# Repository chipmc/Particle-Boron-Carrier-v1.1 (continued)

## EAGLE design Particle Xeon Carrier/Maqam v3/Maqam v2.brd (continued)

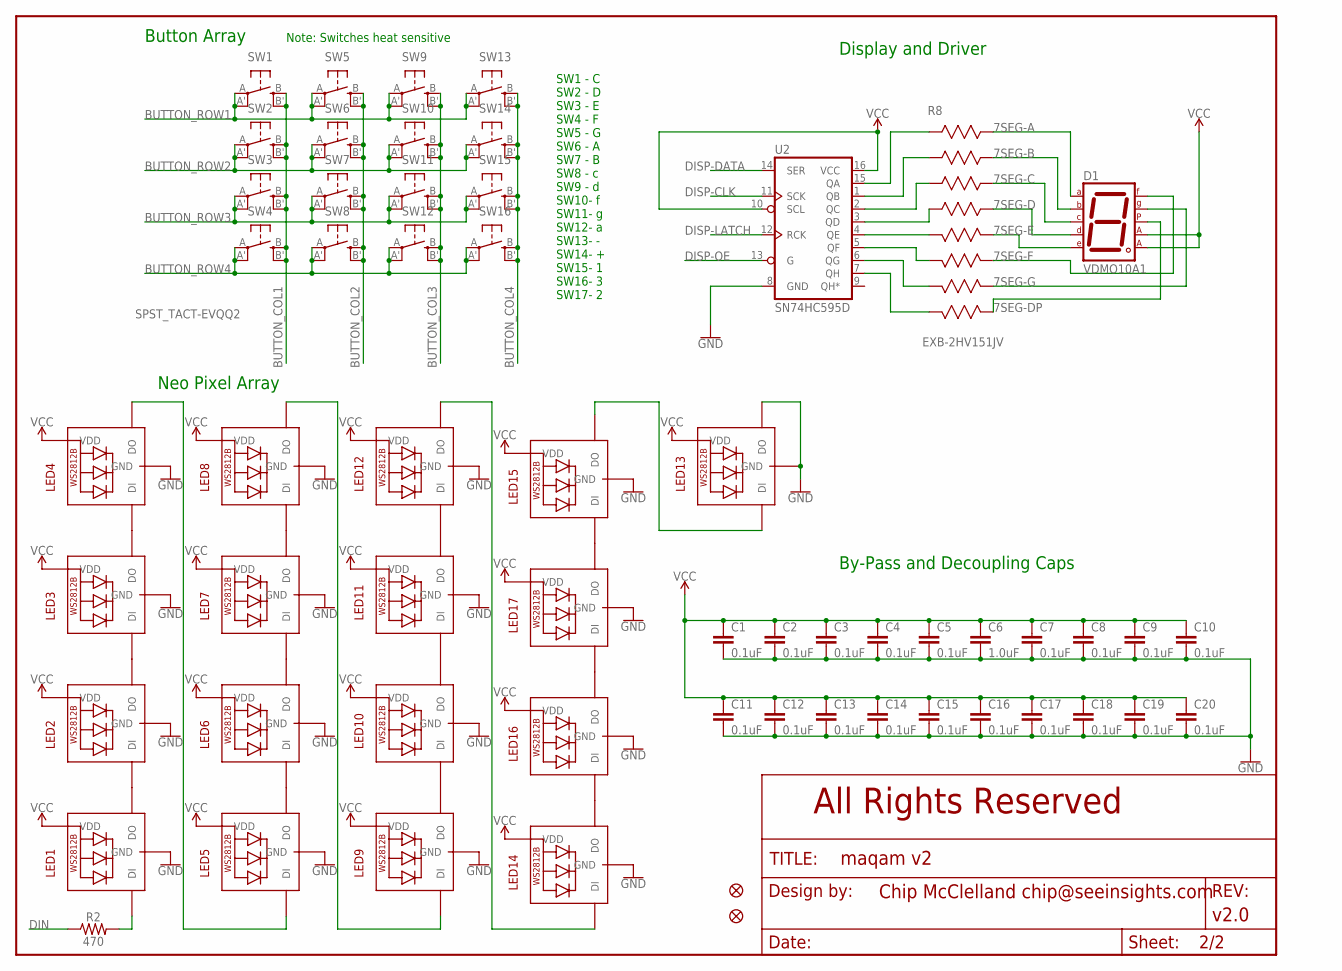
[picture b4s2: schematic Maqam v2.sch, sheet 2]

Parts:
C1, C2, C3, C4, C5, C7, C8, C9, C10, C11, C12, C13, C14, C15, C16, C17, C18, C19, C20: 0.1uF; 0805
C6: 1.0uF; 0805
D1: VDMO10A1; 7-SEG-SMD
FD1, FD2: FIDUCIALUFIDUCIAL; FIDUCIAL-MICRO
FRAME1: FRAME-LETTERNO_PACKAGE; DUMMY
LED1, LED2, LED3, LED4, LED5, LED6, LED7, LED8, LED9, LED10, LED11, LED12, LED13, LED14, LED15, LED16, LED17: WS2812B3535; LED3535
R2: 470; 0805
R8: EXB-2HV151JV; EXB2HV-L
SW1, SW2, SW3, SW4, SW5, SW6, SW7, SW8, SW9, SW10, SW11, SW12, SW13, SW14, SW15, SW16: SPST_TACT-EVQQ2; EVQ-Q2
U2: SN74HC595D; SO16

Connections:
7SEG-A: D1.7SEG7 (A), R8.16 (162)
7SEG-B: D1.7SEG6 (B), R8.15 (154)
7SEG-C: D1.7SEG4 (C), R8.14 (146)
7SEG-D: D1.7SEG2 (D), R8.13 (138)
7SEG-DP: D1.7SEG5 (DP), R8.9 (912)
7SEG-E: D1.7SEG1 (E), R8.12 (1211)
7SEG-F: D1.7SEG9 (F), R8.11 (1110)
7SEG-G: D1.7SEG10 (G), R8.10 (109)
BUTTON_COL1: SW1.B (S), SW1.B' (S1), SW2.B (S), SW2.B' (S1), SW3.B (S), SW3.B' (S1), SW4.B (S), SW4.B' (S1); also elsewhere on the board
BUTTON_COL2: SW5.B (S), SW5.B' (S1), SW6.B (S), SW6.B' (S1), SW7.B (S), SW7.B' (S1), SW8.B (S), SW8.B' (S1); also elsewhere on the board
BUTTON_COL3: SW9.B (S), SW9.B' (S1), SW10.B (S), SW10.B' (S1), SW11.B (S), SW11.B' (S1), SW12.B (S), SW12.B' (S1); also elsewhere on the board
BUTTON_COL4: SW13.B (S), SW13.B' (S1), SW14.B (S), SW14.B' (S1), SW15.B (S), SW15.B' (S1), SW16.B (S), SW16.B' (S1); also elsewhere on the board
BUTTON_ROW1: SW1.A, SW1.A' (P1), SW5.A, SW5.A' (P1), SW9.A, SW9.A' (P1), SW13.A, SW13.A' (P1); also elsewhere on the board
BUTTON_ROW2: SW2.A, SW2.A' (P1), SW6.A, SW6.A' (P1), SW10.A, SW10.A' (P1), SW14.A, SW14.A' (P1); also elsewhere on the board
BUTTON_ROW3: SW3.A, SW3.A' (P1), SW7.A, SW7.A' (P1), SW11.A, SW11.A' (P1), SW15.A, SW15.A' (P1); also elsewhere on the board
BUTTON_ROW4: SW4.A, SW4.A' (P1), SW8.A, SW8.A' (P1), SW12.A, SW12.A' (P1), SW16.A, SW16.A' (P1); also elsewhere on the board
DIN: R2.1; also elsewhere on the board
DISP-CLK: U2.11 (SCK); also elsewhere on the board
DISP-DATA: U2.14 (SER); also elsewhere on the board
DISP-LATCH: U2.12 (RCK); also elsewhere on the board
DISP-OE: U2.13 (G); also elsewhere on the board
GND: C1.2, C2.2, C3.2, C4.2, C5.2, C6.2, C7.2, C8.2, C9.2, C10.2, C11.2, C12.2, C13.2, C14.2, C15.2, C16.2, C17.2, C18.2, C19.2, C20.2, LED1.4 (GND), LED2.4 (GND), LED3.4 (GND), LED4.4 (GND), LED5.4 (GND), LED6.4 (GND), LED7.4 (GND), LED8.4 (GND), LED9.4 (GND), LED10.4 (GND), LED11.4 (GND), LED12.4 (GND), LED13.3 (DO), LED13.4 (GND), LED14.4 (GND), LED15.4 (GND), LED16.4 (GND), LED17.4 (GND), U2.8 (GND); also elsewhere on the board
unnamed: LED1.3 (DO), LED2.1 (DI)
unnamed: LED3.3 (DO), LED4.1 (DI)
unnamed: LED2.3 (DO), LED3.1 (DI)
unnamed: LED7.3 (DO), LED8.1 (DI)
unnamed: LED6.3 (DO), LED7.1 (DI)
unnamed: LED5.3 (DO), LED6.1 (DI)
unnamed: LED11.3 (DO), LED12.1 (DI)
unnamed: LED10.3 (DO), LED11.1 (DI)
unnamed: LED9.3 (DO), LED10.1 (DI)
unnamed: LED14.3 (DO), LED16.1 (DI)
unnamed: LED4.3 (DO), LED5.1 (DI)
unnamed: LED8.3 (DO), LED9.1 (DI)
unnamed: LED16.3 (DO), LED17.1 (DI)
unnamed: R8.1 (11), U2.15 (QA)
unnamed: LED15.1 (DI), LED17.3 (DO)
unnamed: LED13.1 (DI), LED15.3 (DO)
unnamed: R8.5 (516), U2.4 (QE)
unnamed: R8.2 (23), U2.1 (QB)
unnamed: R8.3 (35), U2.2 (QC)
unnamed: LED1.1 (DI), R2.2
unnamed: R8.4 (47), U2.3 (QD)
unnamed: R8.6 (615), U2.5 (QF)
unnamed: R8.7 (714), U2.6 (QG)
unnamed: R8.8 (813), U2.7 (QH)
unnamed: LED12.3 (DO), LED14.1 (DI)
VCC: C1.1, C2.1, C3.1, C4.1, C5.1, C6.1, C7.1, C8.1, C9.1, C10.1, C11.1, C12.1, C13.1, C14.1, C15.1, C16.1, C17.1, C18.1, C19.1, C20.1, D1.7SEG3 (CA1), D1.7SEG8 (CA2), LED1.2 (VDD), LED2.2 (VDD), LED3.2 (VDD), LED4.2 (VDD), LED5.2 (VDD), LED6.2 (VDD), LED7.2 (VDD), LED8.2 (VDD), LED9.2 (VDD), LED10.2 (VDD), LED11.2 (VDD), LED12.2 (VDD), LED13.2 (VDD), LED14.2 (VDD), LED15.2 (VDD), LED16.2 (VDD), LED17.2 (VDD), U2.10 (SCL), U2.16 (VCC); also elsewhere on the board

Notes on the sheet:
Button Array
Neo Pixel Array
Display and Driver
By-Pass and Decoupling Caps
All Rights Reserved
SW1 - C SW2 - D SW3 - E SW4 - F SW5 - G SW6 - A SW7 - B SW8 - c SW9 - d SW10- f SW11- g SW12- a SW13- - SW14- + SW15- 1 SW16- 3 SW17- 2
Note: Switches heat sensitive

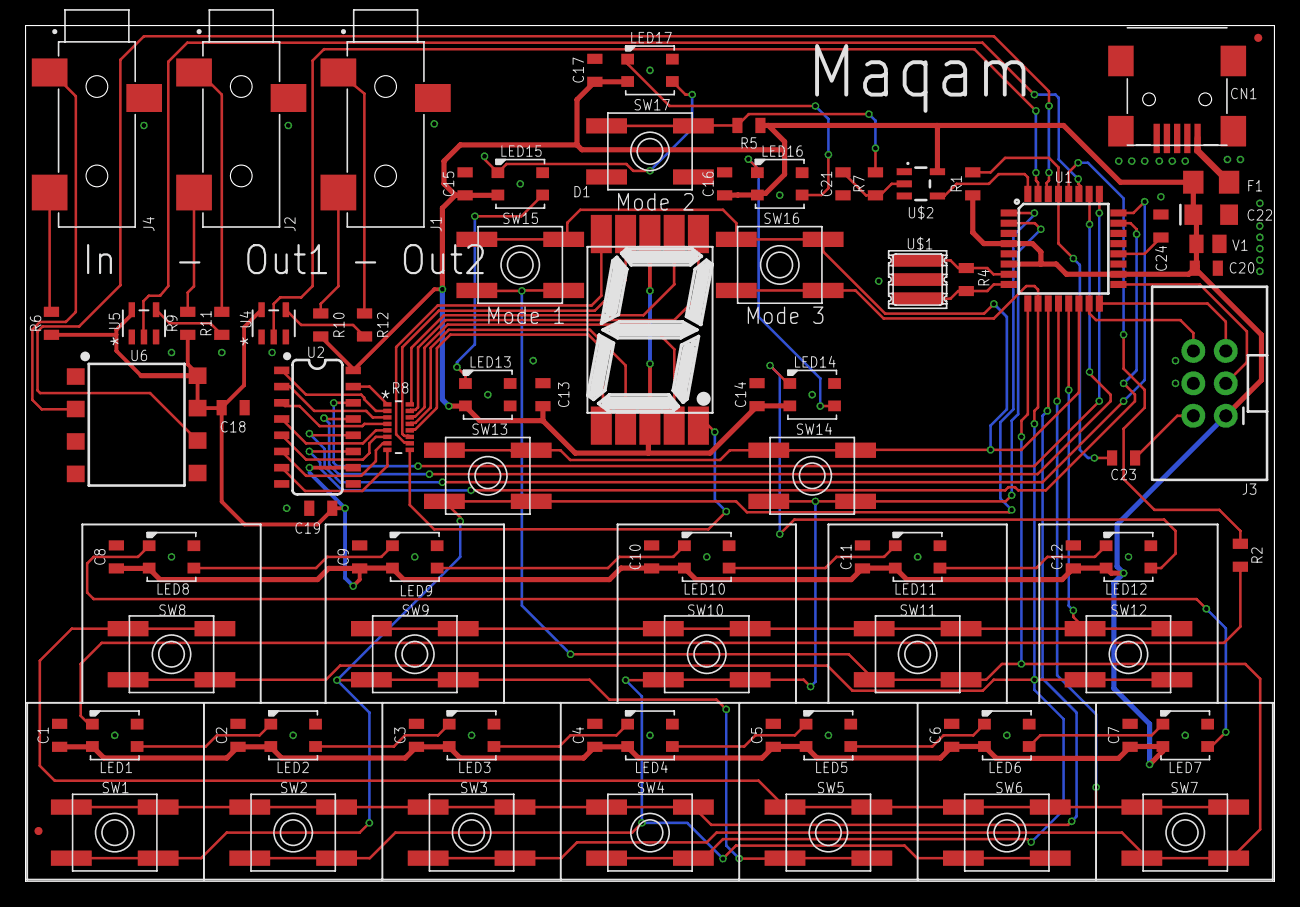
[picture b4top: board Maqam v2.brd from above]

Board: 2 copper layers, 97.8 x 67.0 mm, 88 parts (0 on the bottom side), 71 nets.

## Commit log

2019-09-19 v1.1 - Added a GND pin to serial
2019-09-19 Fixed Analoge Header Pins
2019-10-26 Next major revision - Added RTC
2019-10-29 Added Zener protection for Argon / Xenon
2019-10-31 Final Tweaks before MacroFab
2019-10-31 Version 1.1 with BOM / Gerbers for prototype run.
